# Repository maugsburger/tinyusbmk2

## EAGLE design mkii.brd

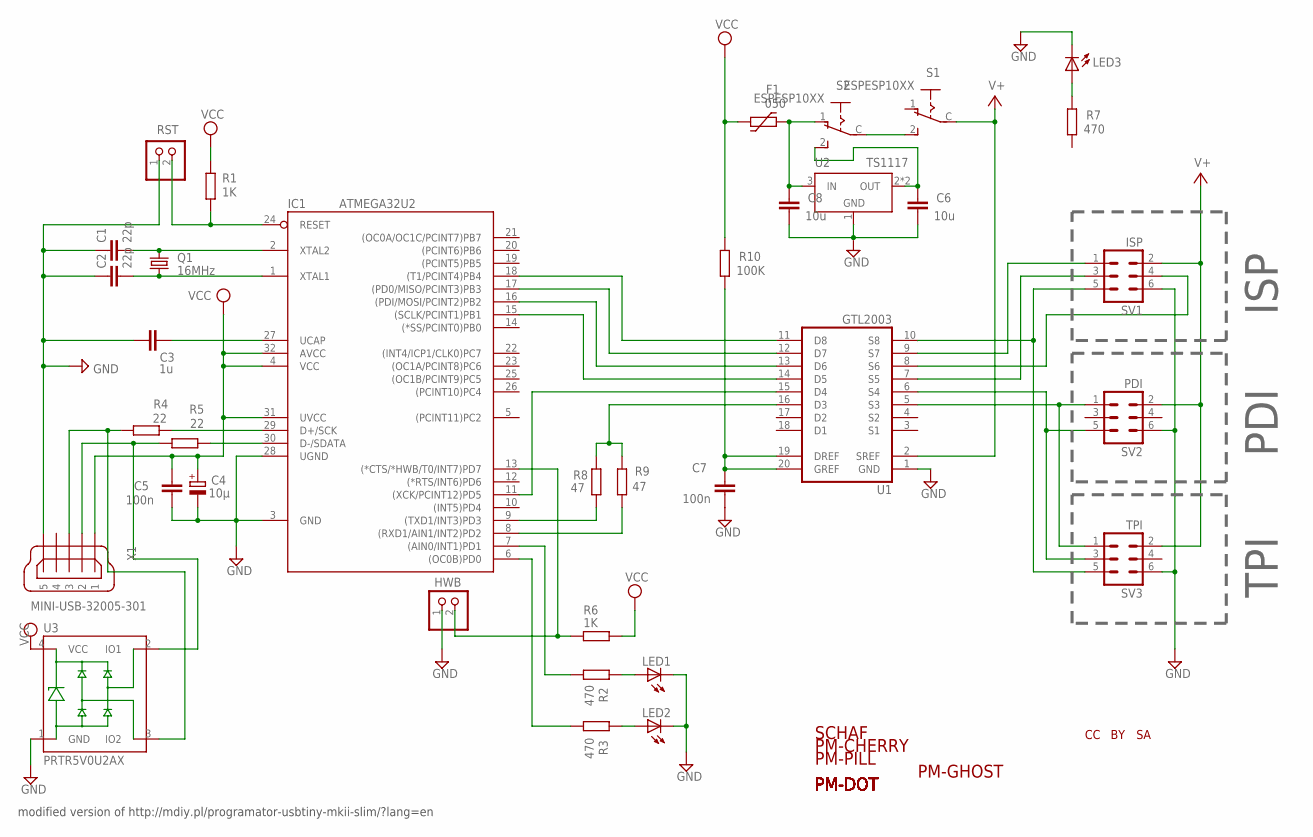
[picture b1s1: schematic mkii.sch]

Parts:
C1, C2: 22p; C0603
C3: 1u; C0805
C4: 10µ; 153CLV-0505
C5, C7: 100n; C0603
C6, C8: 10u; C0805
F1: 050; 1812L
HWB: PINHD-1X02_2.54-S; 1X02-S
IC1: ATMEGA32U2; TQFP32-08
LED1, LED2, LED3: LEDCHIP-LED0603; CHIP-LED0603
Q1: 16MHz; HC49/S
R1, R6: 1K; R0603
R2, R3, R7: 470; R0603
R4, R5: 22; R0603
R8, R9: 47; R0603
R10: 100K; R0603
RST: PINHD-1X02_2.54-S; 1X02-S
S1, S2: ESPESP10XX; ESP10XX
SV1: ISP; ML6
SV2: PDI; ML6
SV3: TPI; ML6
U1: GTL2003; TSSOP20
U2: TS1117; SOT223
U3: PRTR5V0U2AX; SOT143B
U$1: CC-TPLACE-HALF; CC_TPLACE_HS
U$2: BY-TPLACE-HS; BY_TPLACE_HS
U$3: SA-TPLACE-HALF; SA_TPLACE_HS
U$4: SCHAF7MM; SCHAF-7
U$5: PM-CHERRY5; PM-CHERRY-5
U$6: PM-PILL5; PM-PILL-5
U$8, U$9, U$10, U$11, U$12, U$13, U$14, U$15: PM-DOT5
U$16: PM-GHOSTA5; PM-GHOSTA-5
X1: MINI-USB-32005-301; 32005-301

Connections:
!RST: IC1.24 (RESET), R1.1, RST.2
D+: IC1.29 (D+/SCK), R4.1
D-: IC1.30 (D-/SDATA), R5.1
GND: C1.1, C2.1, C3.1, C4.-, C5.1, C6.1, C7.1, C8.1, HWB.1, IC1.3 (GND), IC1.28 (UGND), LED1.C, LED2.C, LED3.C, RST.1, SV1.6, SV2.6, SV3.6, U1.1 (GND), U2.1 (GND), U3.1 (GND), X1.5
HWB: HWB.2, IC1.13 ((*CTS/*HWB/T0/INT7)PD7), R6.1
unnamed: R4.2, U3.3 (IO2), X1.3
unnamed: S1.2 (S), S2.C
unnamed: IC1.7 ((AIN0/INT1)PD1), R2.2
unnamed: LED3.A, R7.1
unnamed: C8.2, F1.P$2 (2), S2.1 (O), U2.3 (IN)
unnamed: R5.2, U3.2 (IO1), X1.2
unnamed: IC1.9 ((TXD1/INT3)PD3), R8.2
unnamed: IC1.6 ((OC0B)PD0), R3.2
unnamed: LED1.A, R2.1
unnamed: LED2.A, R3.1
unnamed: C7.2, R10.2, U1.19 (DREF), U1.20 (GREF)
unnamed: IC1.18 ((T1/PCINT4)PB4), U1.11 (D8)
unnamed: IC1.17 ((PD0/MISO/PCINT3)PB3), U1.12 (D7)
unnamed: IC1.16 ((PDI/MOSI/PCINT2)PB2), U1.13 (D6)
unnamed: IC1.15 ((SCLK/PCINT1)PB1), U1.14 (D5)
unnamed: IC1.11 ((XCK/PCINT12)PD5), U1.15 (D4)
unnamed: R8.1, R9.1, U1.16 (D3)
unnamed: SV2.1, SV3.1, U1.5 (S3)
unnamed: SV2.5, SV3.3, U1.6 (S4)
unnamed: SV1.5, SV3.5, U1.10 (S8)
unnamed: SV1.1, U1.9 (S7)
unnamed: SV1.4, U1.8 (S6)
unnamed: SV1.3, U1.7 (S5)
unnamed: IC1.8 ((RXD1/AIN1/INT2)PD2), R9.2
unnamed: C6.2, S2.2 (S), U2.2 (OUT), U2.4 (OUT)
UCAP: C3.2, IC1.27 (UCAP)
V+: S1.C, SV1.2, SV2.2, SV3.2, U1.2 (SREF)
VCC: C4.+, C5.2, F1.P$1 (1), IC1.4 (VCC), IC1.31 (UVCC), IC1.32 (AVCC), R1.2, R6.2, R10.1, U3.4 (VCC), X1.1
XTAL1: C2.2, IC1.1 (XTAL1), Q1.1
XTAL2: C1.2, IC1.2 (XTAL2), Q1.2

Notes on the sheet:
ISP
PDI
TPI
modified version of http://mdiy.pl/programator-usbtiny-mkii-slim/?lang=en

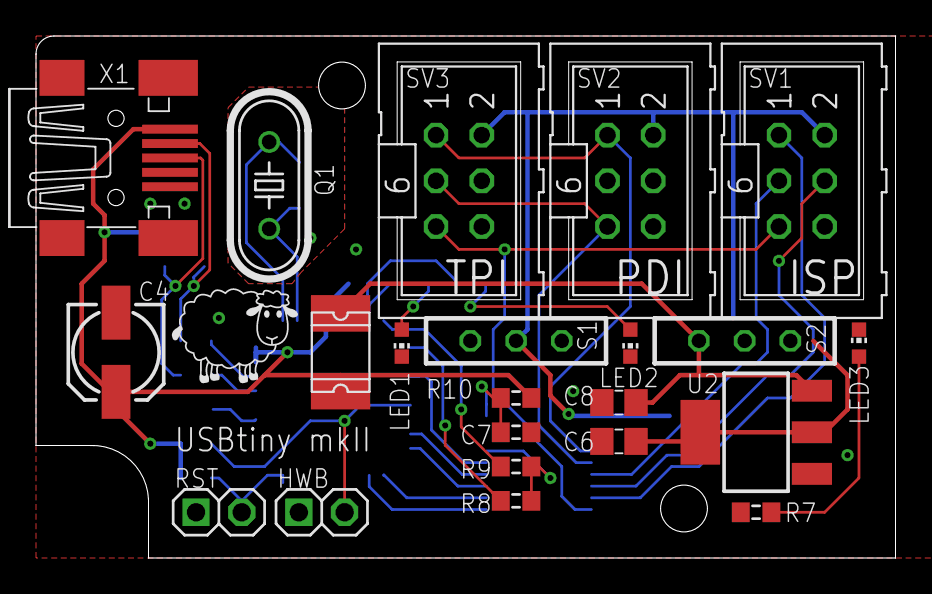
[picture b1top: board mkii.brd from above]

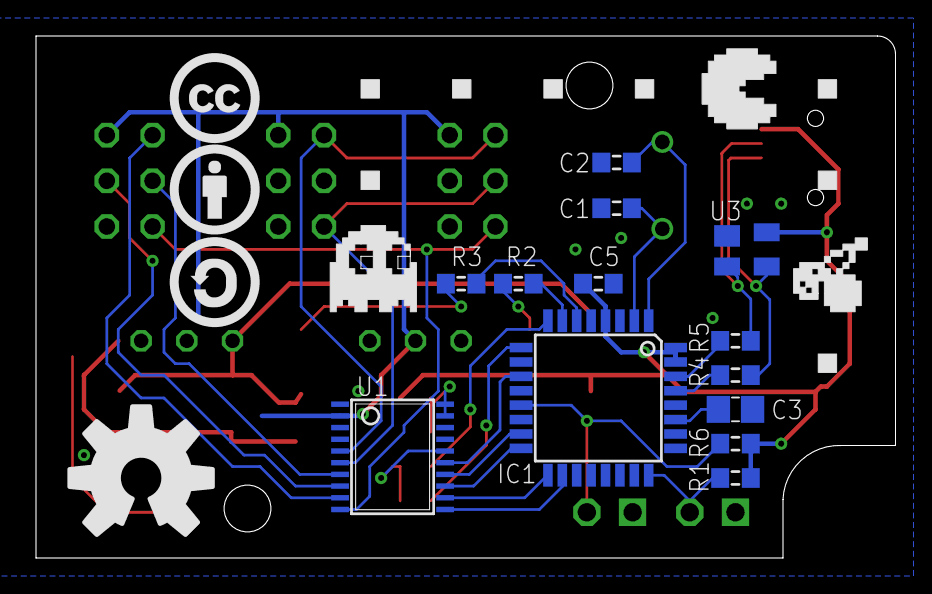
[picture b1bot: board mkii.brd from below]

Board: 2 copper layers, 47.8 x 29.0 mm, 50 parts (27 on the bottom side), 35 nets.

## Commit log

2013-09-26 changed led pins, rearranged everyting
2013-09-26 align silk screen
2013-09-26 sheep power
2013-09-27 pacman arrived
2013-09-29 more gnd plane between data lines
2013-09-29 esd supressor for usb
2013-10-04 growing sheep
2013-10-04 move leds slightly farther away from pin headers
2013-11-05 atmega32u2, not u4
2013-11-05 arranged top/bottom value printout
2013-11-05 22p cap for crystal
2014-02-23 pin4 on usb is id, pin5 is gnd. upstream idiots.
2014-02-23 remote circuit on pb5
    can't remember my thoughts – without ADC there is no vbus
    detection.
2014-02-24 C6/C8 changed to 0805
    10nF in 0603 is hardly available
2015-03-31 unknown changes

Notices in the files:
parts and their libraries:
creative-commons: creative commons
Attribution - BY
